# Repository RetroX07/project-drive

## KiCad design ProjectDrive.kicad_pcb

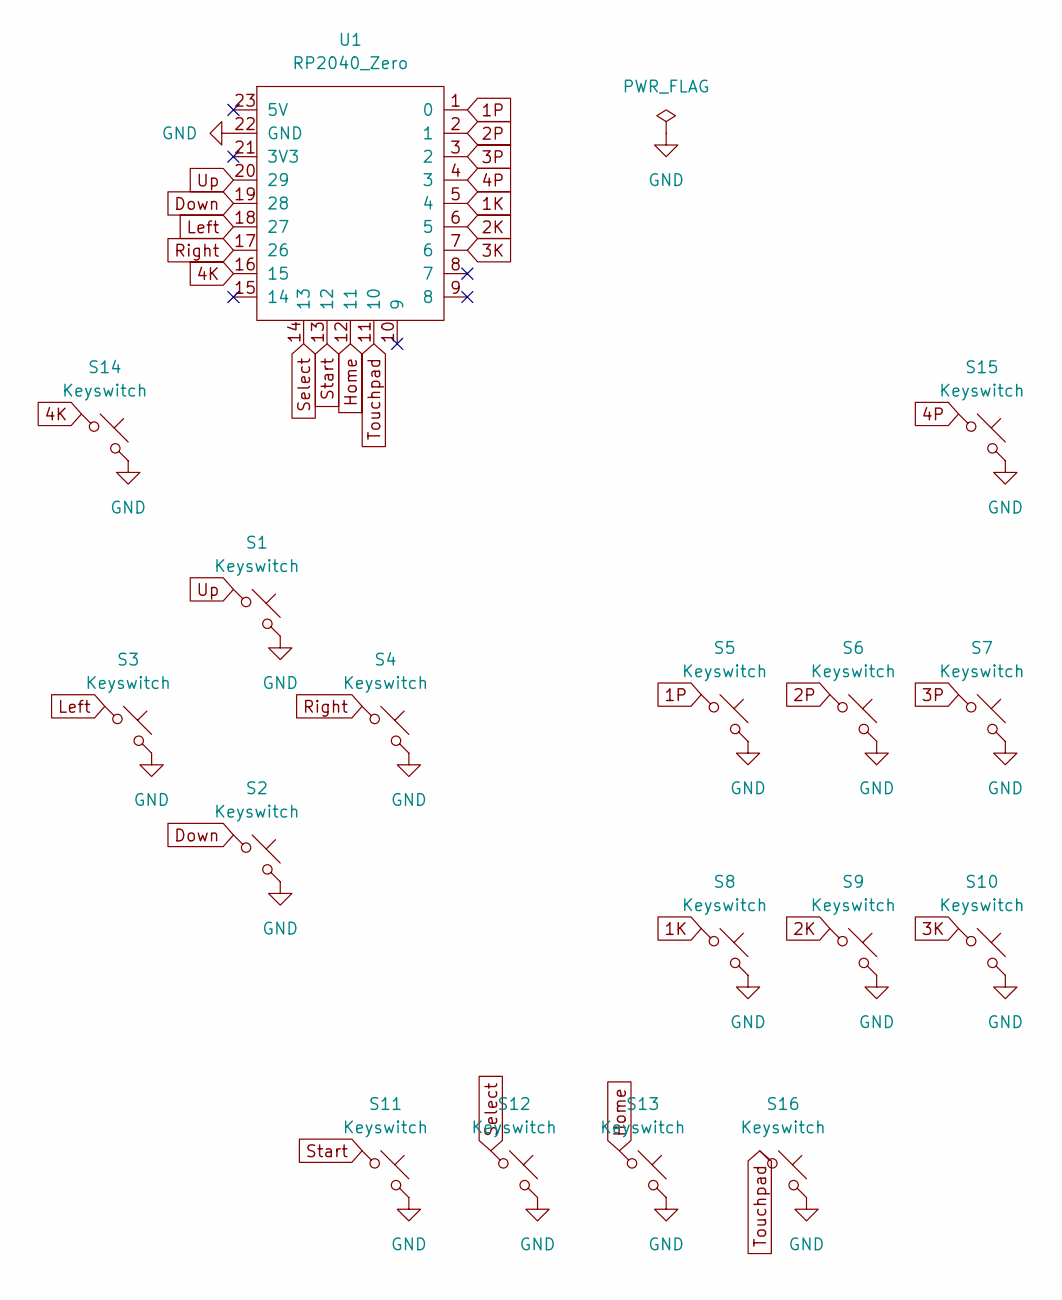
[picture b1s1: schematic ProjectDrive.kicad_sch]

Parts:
S1, S2, S3, S4, S5, S6, S7, S8, S9, S10, S11, S12, S13, S16: Keyswitch; SW_PUSH_6mm_H5mm
S14, S15: Keyswitch; SW_Tactile_SPST_Angled_PTS645Vx39-2LFS
U1: RP2040_Zero

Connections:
1K: S8.1, U1.5 (4)
1P: S5.1, U1.1 (0)
2K: S9.1, U1.6 (5)
2P: S6.1, U1.2 (1)
3K: S10.1, U1.7 (6)
3P: S7.1, U1.3 (2)
4K: S14.1, U1.16 (15)
4P: S15.1, U1.4 (3)
Down: S2.1, U1.19 (28)
GND: S1.2, S2.2, S3.2, S4.2, S5.2, S6.2, S7.2, S8.2, S9.2, S10.2, S11.2, S12.2, S13.2, S14.2, S15.2, S16.2, U1.22 (GND)
Home: S13.1, U1.12 (11)
Left: S3.1, U1.18 (27)
Right: S4.1, U1.17 (26)
Select: S12.1, U1.14 (13)
Start: S11.1, U1.13 (12)
Touchpad: S16.1, U1.11 (10)
Up: S1.1, U1.20 (29)

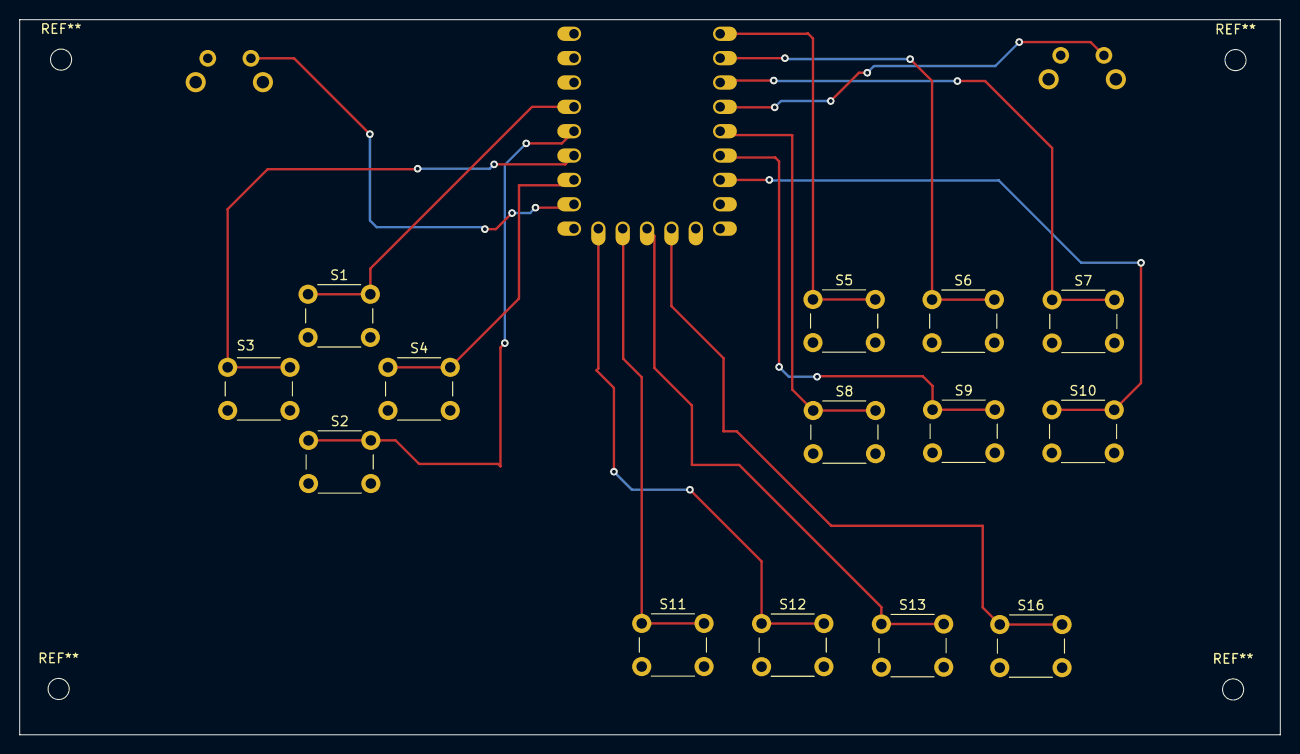
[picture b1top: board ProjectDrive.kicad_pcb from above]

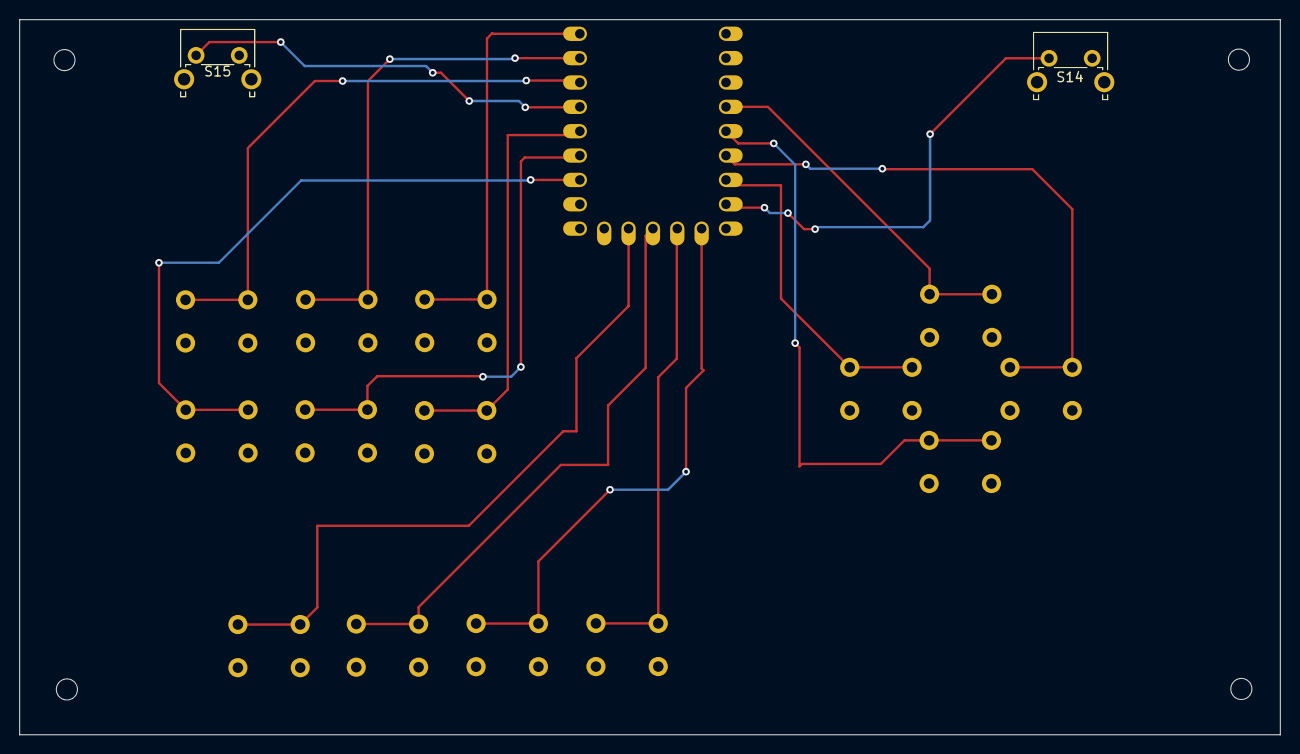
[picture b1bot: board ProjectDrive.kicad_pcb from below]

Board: 2 copper layers, 131.5 x 74.6 mm, 17 parts (2 on the bottom side), 17 nets.

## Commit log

2024-02-04 Base build
2024-02-05 Updated PCB
